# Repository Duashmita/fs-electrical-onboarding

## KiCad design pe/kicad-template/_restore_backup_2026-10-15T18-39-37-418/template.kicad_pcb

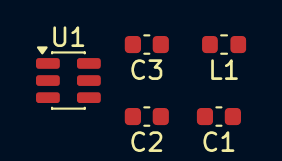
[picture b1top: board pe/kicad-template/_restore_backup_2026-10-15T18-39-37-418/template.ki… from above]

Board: 2 copper layers, 5 parts (0 on the bottom side), 5 nets, no tracks yet.

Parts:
C1: 22uF; C_0603_1608Metric
C2: 1uF; C_0603_1608Metric
C3: 10uF; C_0603_1608Metric
L1: 15uH; L_0603_1608Metric
U1: TPS542025DDCR; SOT-23-6

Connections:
+5V: C1.1, L1.2, U1.3 (VIN)
+15V: C3.1, U1.4 (FB)
GND: C1.2, C3.2, U1.6 (VBST)
unnamed: C2.2, L1.1, U1.5 (EN)
unnamed: C2.1, U1.1 (GND)

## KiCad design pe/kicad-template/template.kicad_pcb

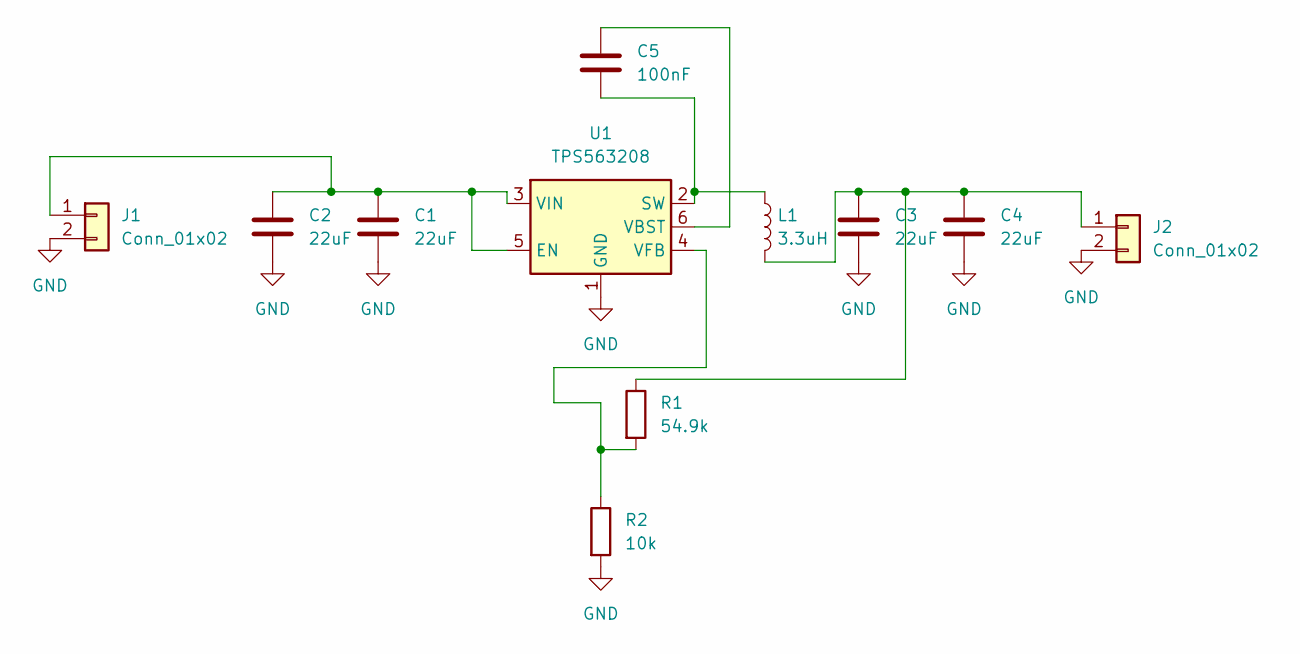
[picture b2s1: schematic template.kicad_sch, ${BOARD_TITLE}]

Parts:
C1, C2, C3, C4: 22uF; C_1210_3225Metric
C5: 100nF; C_0603_1608Metric
J1, J2: Conn_01x02; PinHeader_1x02_P2.54mm_Vertical
L1: 3.3uH; L_Wuerth_WE-PD-Typ-M-Typ-S
R1: 54.9k; R_0603_1608Metric
R2: 10k; R_0603_1608Metric
U1: TPS563208; SOT-23-6

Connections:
GND: C1.2, C2.2, C3.2, C4.2, J1.2, J2.2, R2.2, U1.1 (GND)
unnamed: C1.1, C2.1, J1.1, U1.3 (VIN), U1.5 (EN)
unnamed: C3.1, C4.1, J2.1, L1.2, R1.1
unnamed: C5.2, L1.1, U1.2 (SW)
unnamed: C5.1, U1.6 (VBST)
unnamed: R1.2, R2.1, U1.4 (VFB)

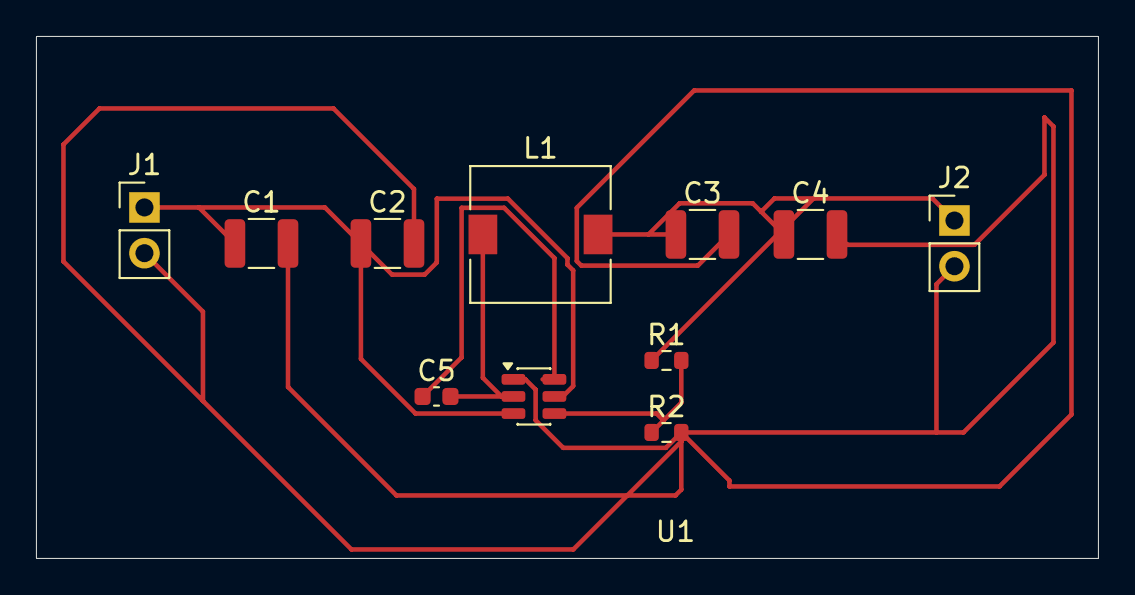
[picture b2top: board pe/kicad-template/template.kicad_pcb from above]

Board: 2 copper layers, 59.0 x 29.0 mm, 11 parts (0 on the bottom side), 6 nets.

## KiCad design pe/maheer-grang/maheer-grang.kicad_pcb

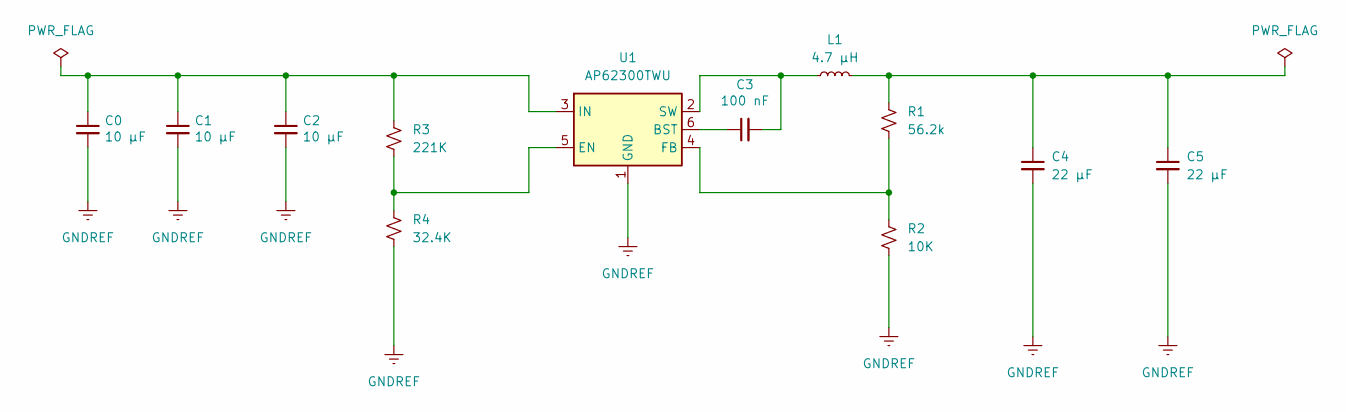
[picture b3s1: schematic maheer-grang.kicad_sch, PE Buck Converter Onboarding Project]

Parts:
C0, C1, C2: 10 µF; C_0603_1608Metric_Pad1.08x0.95mm_HandSolder; Manufacturer Part Number GRM188R61E106MA73J; Digikey Part Number 490-12737-1-ND
C3: 100 nF; C_0603_1608Metric_Pad1.08x0.95mm_HandSolder; Manufacturer Part Number CC0603KRX7R9BB104; Digikey Part Number 311-1344-1-ND
C4, C5: 22 µF; C_0603_1608Metric_Pad1.08x0.95mm_HandSolder; Manufacturer Part Number 0603YD226MAT2A; Digikey Part Number 478-KGM15CR51C226MTCT-ND
L1: 4.7 µH; L_Pulse_PA4332; Manufacturer Part Number CSEG0430H-4R7M; Digikey Part Number 4044-CSEG0430H-4R7MTR-ND
R1: 56.2k; R_0603_1608Metric_Pad0.98x0.95mm_HandSolder; Manufacturer Part Number RC0603FR-0756K2L; Digikey Part Number 311-56.2KHRCT-ND
R2: 10K; R_0603_1608Metric_Pad0.98x0.95mm_HandSolder; Manufacturer Part Number AC0603FR-0710KL; Digikey Part Number 311-10KLDCT-ND
R3: 221K; R_0603_1608Metric_Pad0.98x0.95mm_HandSolder; Manufacturer Part Number AC0603FR-07221KL; Digikey Part Number 13-AC0603FR-07221KLCT-ND
R4: 32.4K; R_0603_1608Metric_Pad0.98x0.95mm_HandSolder; Manufacturer Part Number AC0603FR-0732K4L; Digikey Part Number 13-AC0603FR-0732K4LCT-ND
U1: AP62300TWU; TSOT-23-6

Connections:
GNDREF: C0.2, C1.2, C2.2, C4.2, C5.2, R2.2, R4.2, U1.1 (GND)
unnamed: C4.1, C5.1, L1.2, R1.1
unnamed: C3.1, U1.6 (BST)
unnamed: R3.2, R4.1, U1.5 (EN)
unnamed: R1.2, R2.1, U1.4 (FB)
unnamed: C0.1, C1.1, C2.1, R3.1, U1.3 (IN)
unnamed: C3.2, L1.1, U1.2 (SW)

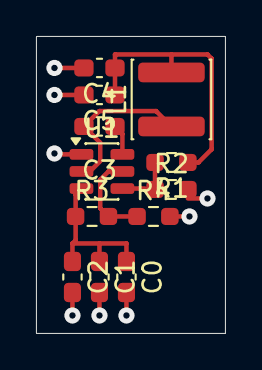
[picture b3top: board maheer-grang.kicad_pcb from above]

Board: 2 copper layers, 10.5 x 16.5 mm, 12 parts (0 on the bottom side), 7 nets.

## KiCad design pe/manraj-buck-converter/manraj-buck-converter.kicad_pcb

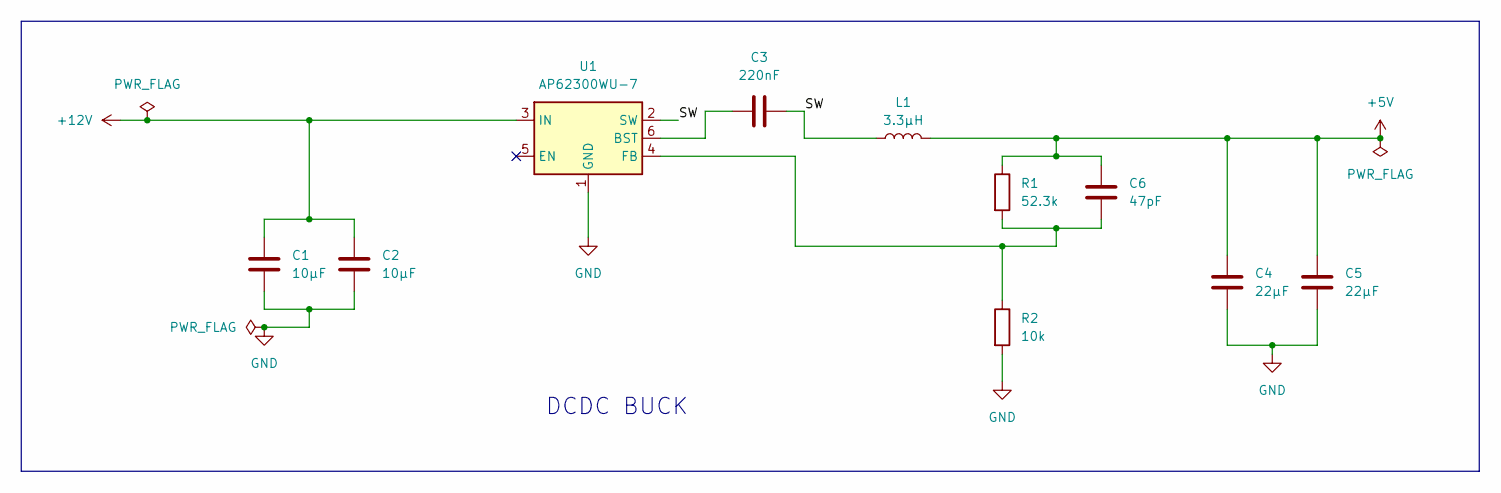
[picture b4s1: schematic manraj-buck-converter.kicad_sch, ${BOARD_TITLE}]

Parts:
C1, C2: 10µF; C_1206_3216Metric_Pad1.33x1.80mm_HandSolder; Manufacturer Part Number CGA5L1X7R1H106K160AC; Digikey Part Number 445-180362-1-ND
C3: 220nF; C_0603_1608Metric_Pad1.08x0.95mm_HandSolder; Manufacturer Part Number GCM188R71H224KA64J; Digikey Part Number 490-13307-1-ND
C4, C5: 22µF; C_1206_3216Metric_Pad1.33x1.80mm_HandSolder; Manufacturer Part Number GRM31CZ71C226ME15L; Digikey Part Number 490-GRM31CZ71C226ME15LCT-ND
C6: 47pF; C_0603_1608Metric_Pad1.08x0.95mm_HandSolder; Manufacturer Part Number CGA3E2C0G1H470J080AA; Digikey Part Number 445-5636-1-ND
L1: 3.3µH; L_Bourns_SRP7028A_7.3x6.6mm; Manufacturer Part Number SRP7028A-3R3M; Digikey Part Number SRP7028A-3R3MCT-ND
R1: 52.3k; R_0603_1608Metric_Pad0.98x0.95mm_HandSolder; Manufacturer Part Number ERJ-3EKF5232V; Digikey Part Number P52.3KHCT-ND
R2: 10k; R_0603_1608Metric_Pad0.98x0.95mm_HandSolder; Manufacturer Part Number ERJ-3EKF1002V; Digikey Part Number P10.0KHCT-ND
U1: AP62300WU-7; TSOT-23-6; Manufacturer Part Number AP62300WU-7; Digikey Part Number 31-AP62300WU-7CT-ND

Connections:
+5V: C4.1, C5.1, C6.1, L1.2, R1.1
+12V: C1.1, C2.1, U1.3 (IN)
/SW: C3.2, L1.1, U1.2 (SW)
GND: C1.2, C2.2, C4.2, C5.2, R2.2, U1.1 (GND)
unnamed: C3.1, U1.6 (BST)
unnamed: C6.2, R1.2, R2.1, U1.4 (FB)

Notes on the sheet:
DCDC BUCK

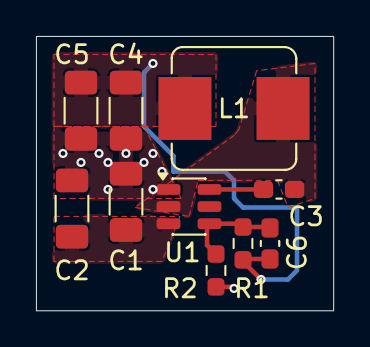
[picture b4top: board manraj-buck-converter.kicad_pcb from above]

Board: 2 copper layers, 16.5 x 15.2 mm, 10 parts (0 on the bottom side), 6 nets.

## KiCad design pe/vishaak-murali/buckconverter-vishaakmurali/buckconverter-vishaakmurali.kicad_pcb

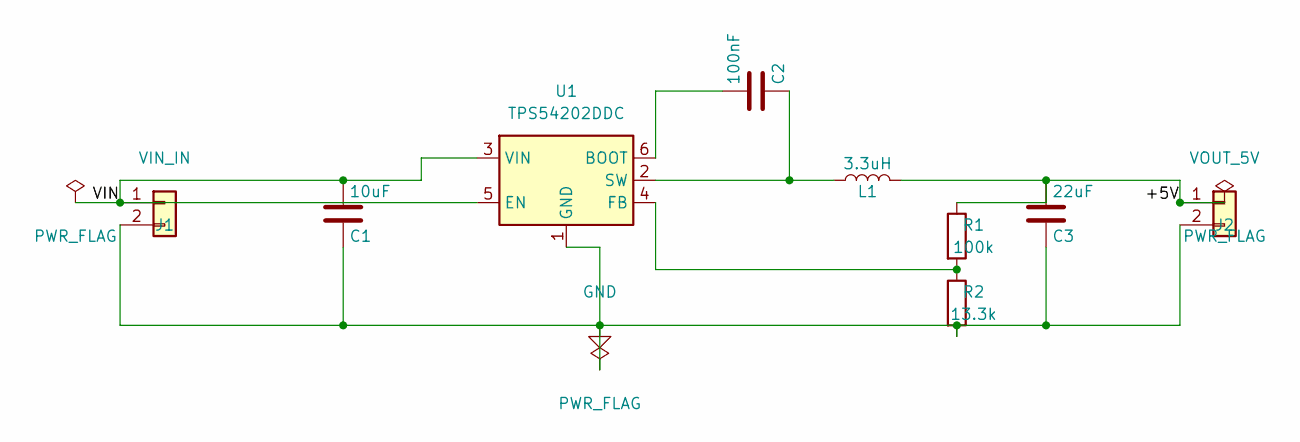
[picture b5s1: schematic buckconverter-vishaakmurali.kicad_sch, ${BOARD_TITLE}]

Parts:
C1: 10uF; C_0805_2012Metric
C2: 100nF; C_0603_1608Metric
C3: 22uF; C_0805_2012Metric
J1: VIN_IN; PinHeader_1x02_P2.54mm_Vertical
J2: VOUT_5V; PinHeader_1x02_P2.54mm_Vertical
L1: 3.3uH; L_Bourns_SRR1260
R1: 100k; R_0603_1608Metric
R2: 13.3k; R_0603_1608Metric
U1: TPS54202DDC; SOT-23-6

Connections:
+5V: C3.1, J2.1, L1.2, R1.1
GND: C1.2, C3.2, J1.2, J2.2, R2.2, U1.1 (GND)
unnamed: C2.1, U1.6 (BOOT)
unnamed: C2.2, L1.1, U1.2 (SW)
unnamed: R1.2, R2.1, U1.4 (FB)
VIN: C1.1, J1.1, U1.3 (VIN), U1.5 (EN)

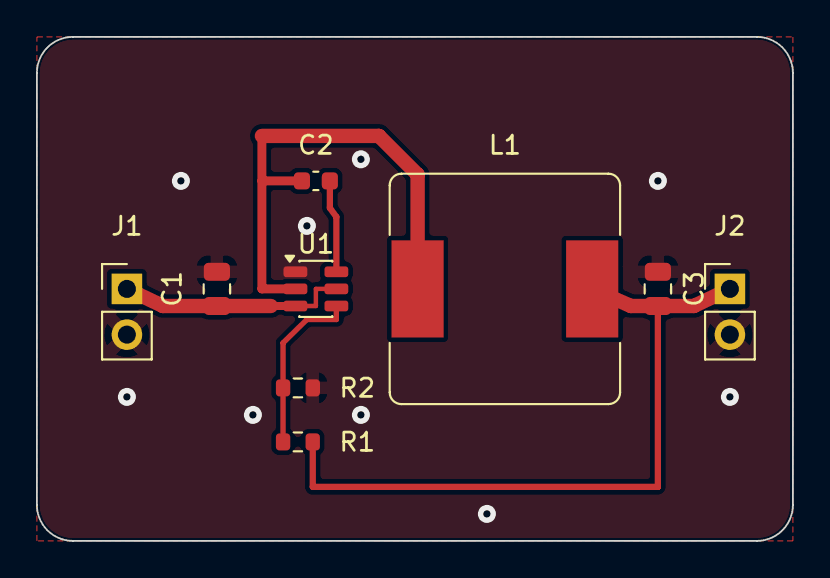
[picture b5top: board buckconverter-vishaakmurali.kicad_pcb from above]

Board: 2 copper layers, 42.0 x 28.0 mm, 9 parts (0 on the bottom side), 6 nets.

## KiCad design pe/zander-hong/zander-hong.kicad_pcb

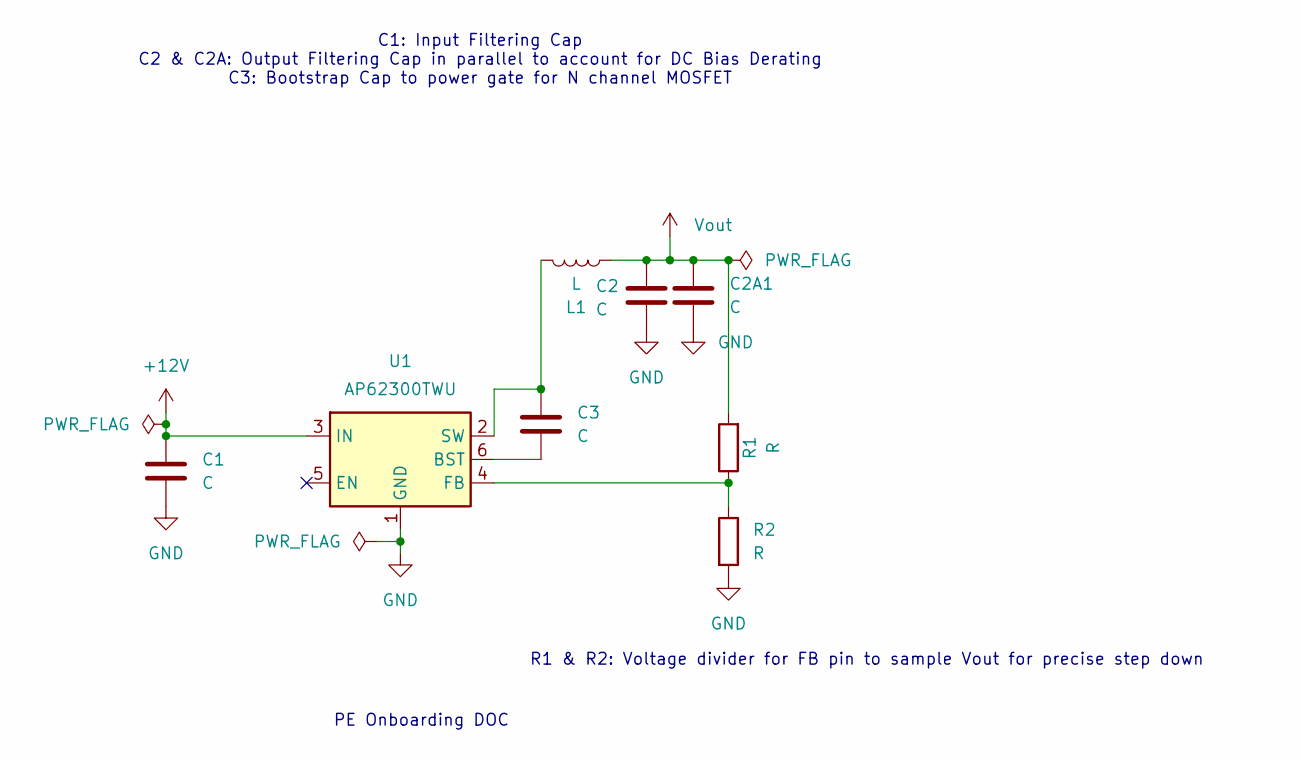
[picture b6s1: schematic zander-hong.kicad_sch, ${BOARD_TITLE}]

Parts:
C1, C2, C2A1, C3: C; C_0603_1608Metric
L1: L; IND_SRP4020_BRN
R1, R2: R; R_0603_1608Metric
U1: AP62300TWU; TSOT-23-6; Digikey Part Number 31-AP62300TWU-7CT-ND

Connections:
+12V: C1.2, U1.3 (IN)
GND: C1.1, C2.1, C2A1.2, R2.2, U1.1 (GND)
unnamed: C3.2, U1.6 (BST)
unnamed: R1.1, R2.1, U1.4 (FB)
unnamed: C3.1, L1.2, U1.2 (SW)
Vout: C2.2, C2A1.1, L1.1, R1.2

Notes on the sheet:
PE Onboarding DOC
C1: Input Filtering Cap C2 & C2A: Output Filtering Cap in parallel to account for DC Bias Derating C3: Bootstrap Cap to power gate for N channel MOSFET
R1 & R2: Voltage divider for FB pin to sample Vout for precise step down

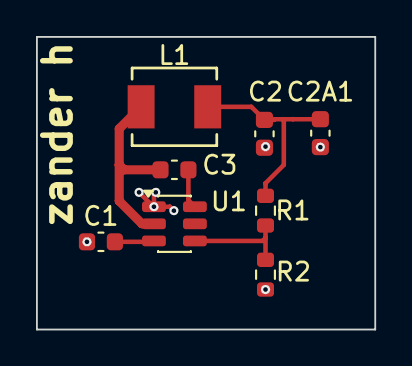
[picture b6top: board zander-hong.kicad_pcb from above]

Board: 2 copper layers, 18.8 x 16.3 mm, 8 parts (0 on the bottom side), 6 nets.
